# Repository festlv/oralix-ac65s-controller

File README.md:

# Misc. tools for Gendex Oralix AC65s control

Schematics is a bit stale- initially it was drawn for Arduino Nano, but couldn't find one, 
so a random ESP32 based module was used instead (which was not a bad idea because WiFi provides
better galvanic isolation than shady circuit wired up on perfboard).

ESP32 firmware is however stable- it was initially tested using 12VAC input to allow safe probing
of signals in order to verify the zero crossing detection and pulse timing accuracy.

Description of Gendex Oralix AC tube: https://nucwiki.org/wiki/index.php/Gendex_Oralix_AC

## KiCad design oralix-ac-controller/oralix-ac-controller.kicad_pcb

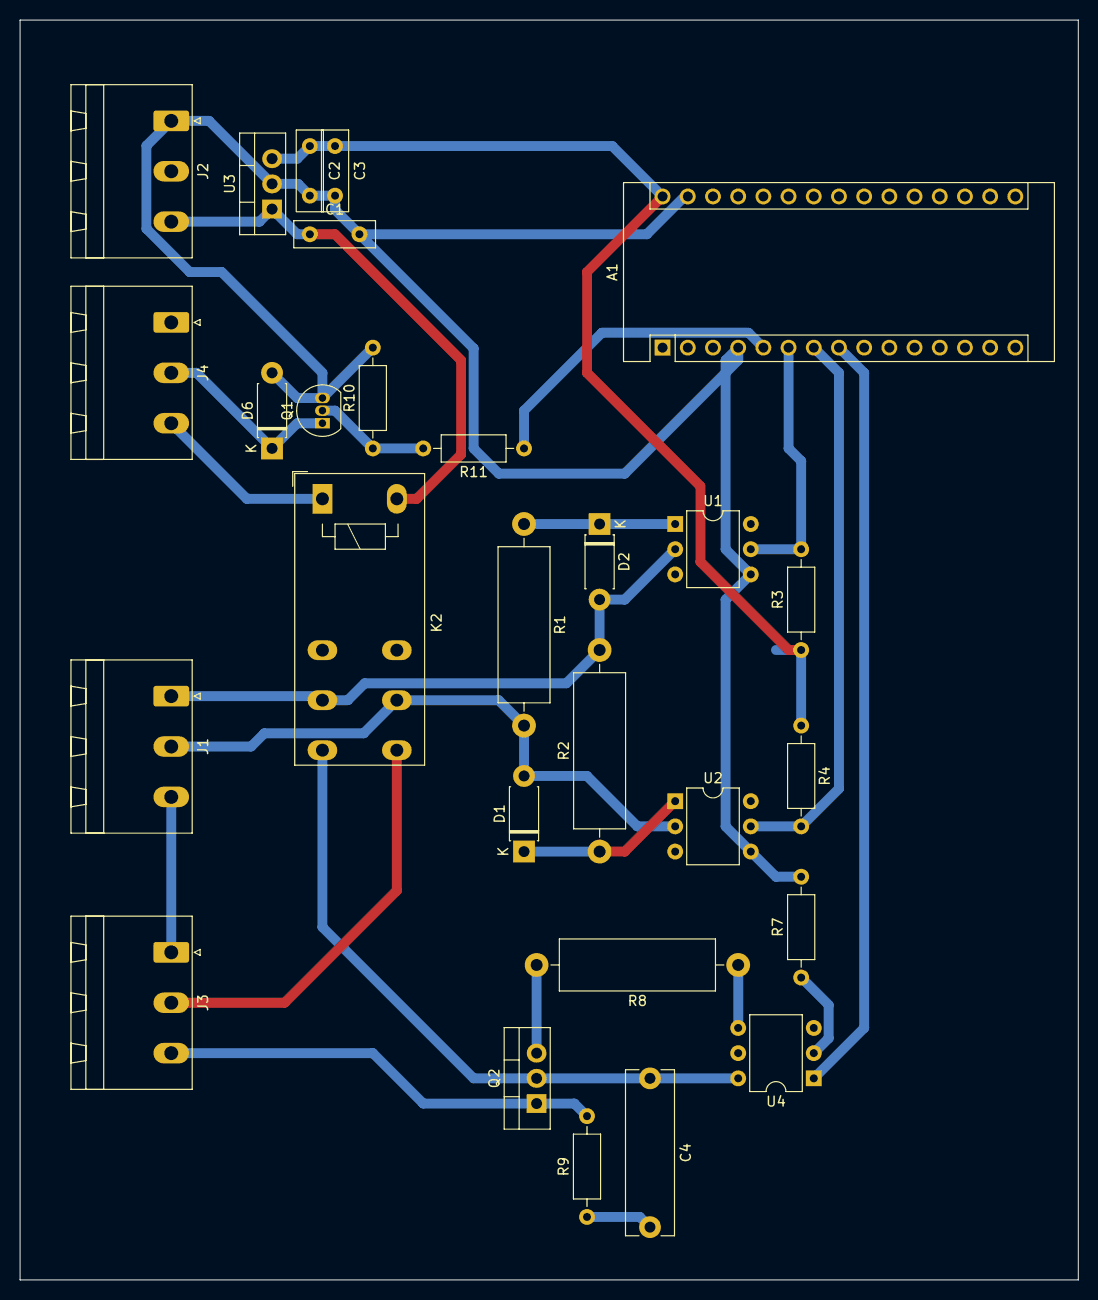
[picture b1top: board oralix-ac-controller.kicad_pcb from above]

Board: 2 copper layers, 106.7 x 127.0 mm, 28 parts (0 on the bottom side), 22 nets.

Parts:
A1: Arduino_Nano_v2.x; Arduino_Nano
C1, C2: 10uF; C_Disc_D8.0mm_W2.5mm_P5.00mm
C3: 0.1uF; C_Disc_D8.0mm_W2.5mm_P5.00mm
C4: 10nF; C_Rect_L16.5mm_W4.7mm_P15.00mm_MKT
D1, D2, D6: 1N4005; D_DO-41_SOD81_P7.62mm_Horizontal
J1, J2, J3, J4: MC000027; PhoenixContact_MSTBA_2,5_3-G-5,08_1x03_P5.08mm_Horizontal
K2: RT424012; Relay_DPDT_Schrack-RT2-FormC_RM5mm
Q1: BC548; TO-92_Inline
Q2: BT138-600; TO-220-3_Vertical
R1, R2: 47K 2W; R_Axial_DIN0516_L15.5mm_D5.0mm_P20.32mm_Horizontal
R3, R4, R10: 10K; R_Axial_DIN0207_L6.3mm_D2.5mm_P10.16mm_Horizontal
R7: 560R; R_Axial_DIN0207_L6.3mm_D2.5mm_P10.16mm_Horizontal
R8: 330R 2W; R_Axial_DIN0516_L15.5mm_D5.0mm_P20.32mm_Horizontal
R9: 39R; R_Axial_DIN0207_L6.3mm_D2.5mm_P10.16mm_Horizontal
R11: 1K; R_Axial_DIN0207_L6.3mm_D2.5mm_P10.16mm_Horizontal
U1, U2: 4N35; DIP-6_W7.62mm
U3: LM7805_TO220; TO-220-3_Vertical
U4: MOC3051M; DIP-6_W7.62mm

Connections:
+5V: A1.30, C2.1, C3.1, R3.1, R4.1, U3.3
+12V: C1.1, J2.3, K2.A2, U3.1
/ENABLE_IN: A1.5, R11.1
/L: D2.2, J1.1, K2.11, R2.2, U1.2
/MAINS_OUT: A1.8, U4.1
/N: D1.2, J1.2, K2.21, R1.2, U2.2
/ZERO_CROSSING_NEG: A1.7, R4.2, U2.5
/ZERO_CROSSING_POS: A1.6, R3.2, U1.5
Earth_Protective: J1.3, J3.1
GND: A1.4, A1.29, C1.2, C2.2, C3.2, D6.2, J2.1, Q1.3, R7.2, R10.2, U1.4, U2.4, U3.2
MAINS_L: C4.1, K2.14, Q2.2, U4.6
MAINS_N: J3.2, K2.24
unnamed: C4.2, R9.1
unnamed: D1.1, R2.1, U2.1
unnamed: D2.1, R1.1, U1.1
unnamed: D6.1, J4.2, Q1.1
unnamed: J3.3, Q2.1, R9.2
unnamed: J4.3, K2.A1
unnamed: Q1.2, R10.1, R11.2
unnamed: Q2.3, R8.2
unnamed: R7.1, U4.2
unnamed: R8.1, U4.4

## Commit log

2020-07-18 Initial working version, implements zero crossing detection and triac control
2020-07-18 Added xray tube controller hardware source (in kicad)
2020-07-18 Added LTSpice sim of zero-crossing detector part
2020-07-18 Create LICENSE
2022-04-14 Add UART as command channel
2022-04-14 Prefix responses with OK/FAIL to make automated parsing easier
